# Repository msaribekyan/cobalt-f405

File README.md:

# Cobalt F405

## An open source flight controller based on the STM32F405 microcontroller

Custom designed flight controller for quadcopters and more.

<div style="text-align:center;">

</div>

## Features

Cobalt F405 flight controller has the following features:
- 4 motor outputs
- barometer and blackbox
- analog on-screen display
- easy-to-use connectors for camera and VTx
- USB Type-C connector for configuration
- high power 5 volt regulator

## Firmware

The flight controller was tested with the [Betaflight](https://github.com/betaflight/betaflight) firmware.

<div style="text-align:center;">

</div>

## Designing

KiCad was used for designing the schematic and the PCB.

### Schematic

<div style="text-align:center;">

</div>

### PCB 3D model

<div style="text-align:center;">

</div>

## Further improvements

### Microcontroller

Although the STM32F405 is still a good choice for flight controllers today, other more powerful microcontrollers also exist. [Betaflight guidlines](https://betaflight.com/docs/development/manufacturer/manufacturer-design-guidelines) suggest not using more than 4 motor outputs for STM32F4 or STM32F7 type microcontrollers.

### PCB

Two layer PCB is fine, however going to a four layer PCB with ground planes inside would reduce electrical noise, which would benefit the microcontroller and the on-board sensors.

### 9 volt regulator

Some external peripherals require higher voltage than 5 volts, however cannot accept 25 volts straight from a 6S battery. A 9 volt regulator can be added to solve this issue.

### More pads and connectors

More pads on the PCB would make it more flexible and easier to use in application. Camera and VTx connectors can be moved to more suitable locations and a connector for the radio receiver could be added.

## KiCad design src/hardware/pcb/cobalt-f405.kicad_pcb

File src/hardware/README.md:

# The hardware

The PCB was design using [KiCad](https://gitlab.com/kicad/code/kicad), an open source schematic and PCB design software.

## Microcontroller: STM32F405RGT6

Betaflight has a list of supported microcontrollers and the STM32F405RGT6, because it is the most common and economical choice while providing enough performance.

## Inertial measurement unit: ICM-42688-P

The [Betaflight Flight Controller Manufacturer Design Guidelines](https://betaflight.com/docs/development/manufacturer/manufacturer-design-guidelines) strongly recommends against using the MPU6000 as it is end-of-life. Instead ICM-42688-P is suggested.

## Barometer: BMP388

Newer model of the BMP180 and BMP280 barometers.

## Blackbox: W25Q128JVP

Winbond W25Q128JVPIQ is a cheap and common 16 MB NOR Flash chip, with a small WSON-8 footprint.

## On-screen display: AT7456E

The flight controller has an on-screen display, for use with analog video. AT7456E is the standard choice.

## Connectors

An 8 pin JST connector is the standard for connecting to the ESC. Telemetry data is connected to UART 1 RX. The two Molex PicoBlade connectors are for the camera and the video transmitter (VTx). The camera connector passes 5 volt power, while the VTx connector passes battery power for more powerful VTx and also has a SmartAudio pin connected to UART 1 TX.

## UART, I2C and power outputs

UARTs 2 and 3 are available on the solder points, along with the I2C bus and three pairs of 5 volt and ground connections.

## PCB

## Front layers

<div style="text-align:center;">

</div>

### Back layers

<div style="text-align:center;">

</div>

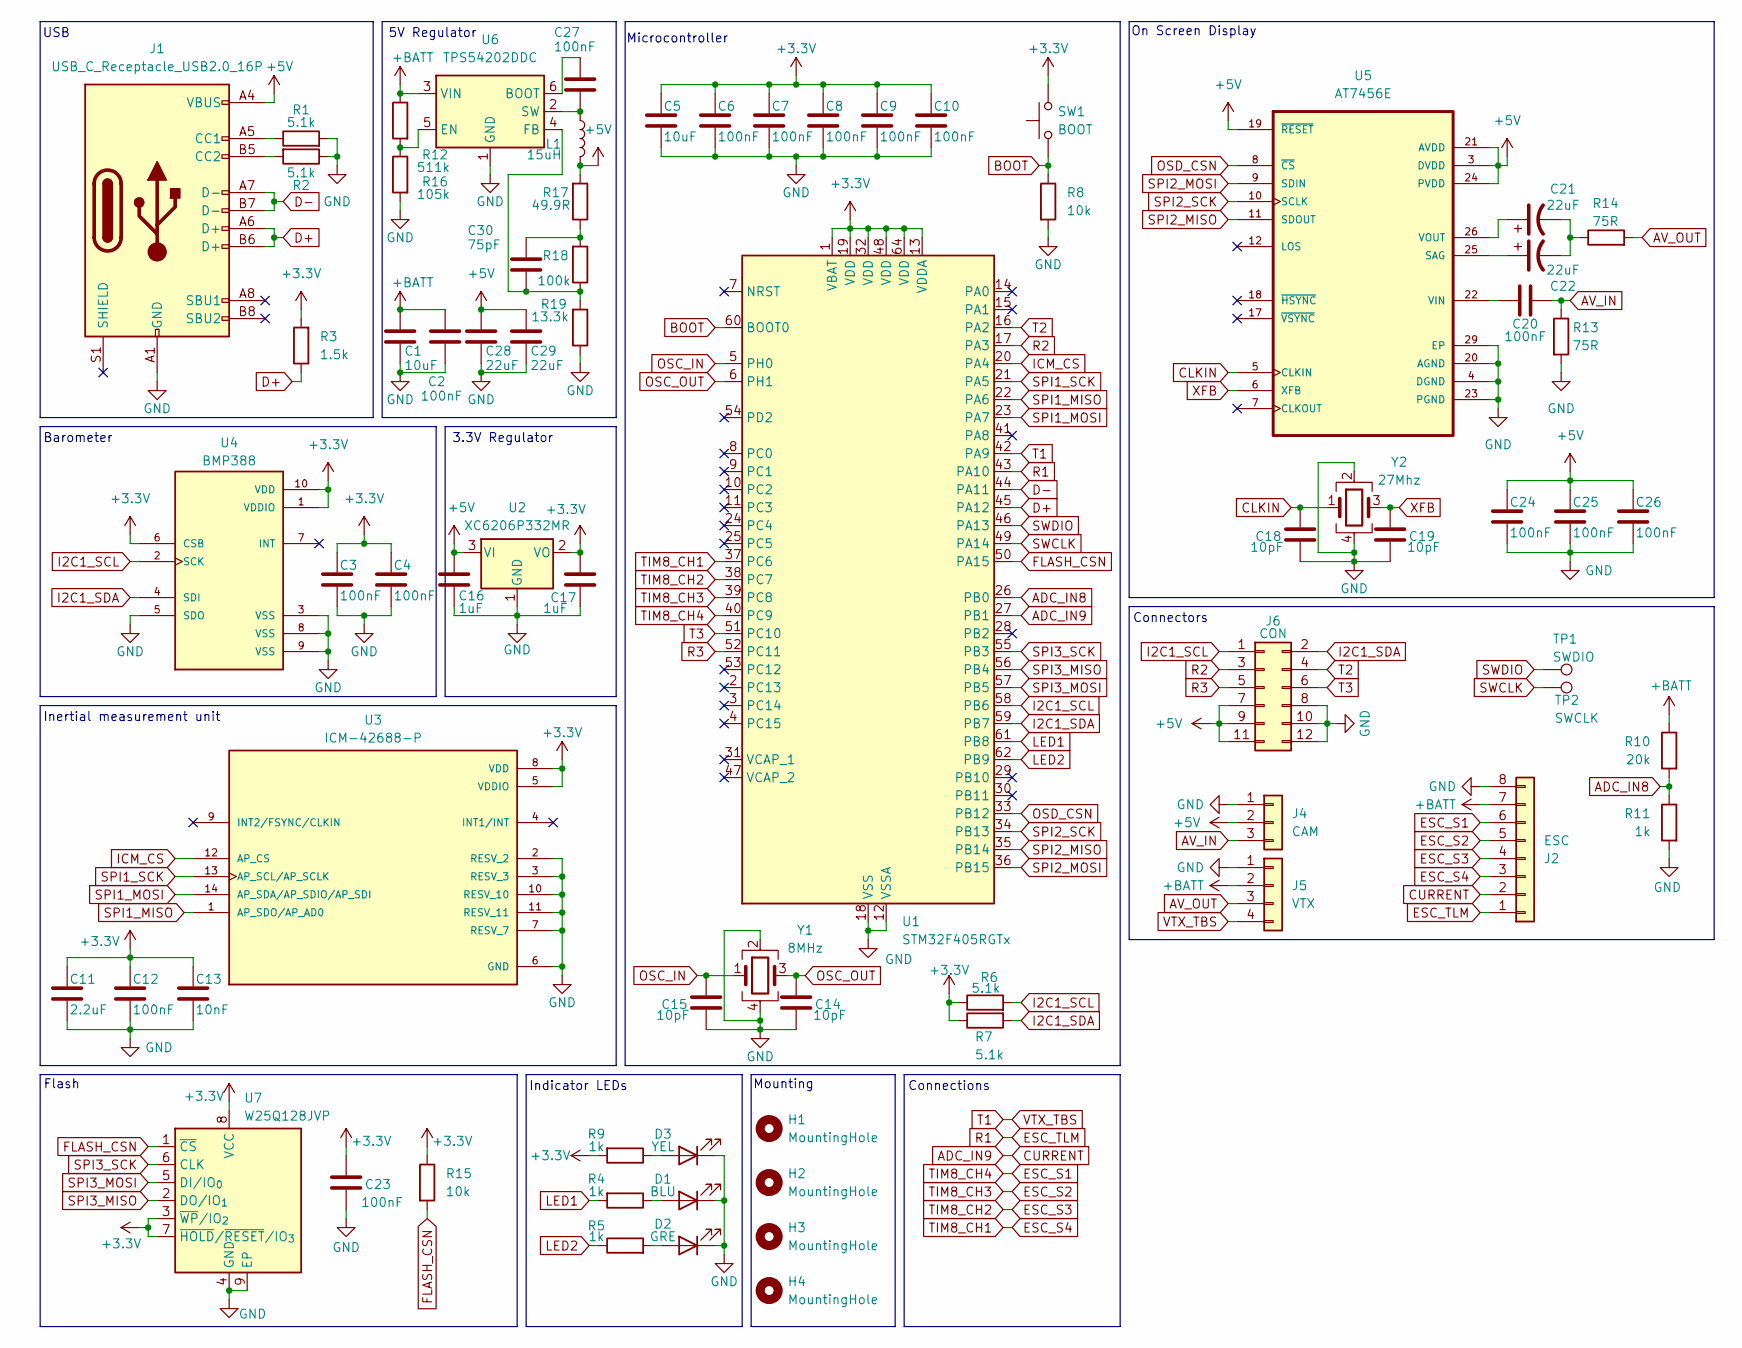
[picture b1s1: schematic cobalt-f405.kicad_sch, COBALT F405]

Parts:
C1, C5: 10uF; C_0603_1608Metric
C2, C8, C20, C23, C27: 100nF; C_0603_1608Metric
C3, C4, C6, C7, C9, C10, C12, C24, C25, C26: 100nF; C_0402_1005Metric
C11: 2.2uF; C_0402_1005Metric
C13: 10nF; C_0402_1005Metric
C14, C15, C18, C19: 10pF; C_0402_1005Metric
C16, C17: 1uF; C_0402_1005Metric
C21, C22, C28, C29: 22uF; C_0603_1608Metric
C30: 75pF; C_0603_1608Metric
D1: BLU; LED_0603_1608Metric
D2: GRE; LED_0603_1608Metric
D3: YEL; LED_0603_1608Metric
H1, H2, H3, H4: MountingHole; MountingHole_4.3mm_M4_ISO14580
J1: USB_C_Receptacle_USB2.0_16P; USB_C_Receptacle_HCTL_HC-TYPE-C-16P-01A
J2: ESC; JST_SH_SM08B-SRSS-TB_1x08-1MP_P1.00mm_Horizontal
J4: CAM; Molex_PicoBlade_53261-0371_1x03-1MP_P1.25mm_Horizontal
J5: VTX; Molex_PicoBlade_53261-0471_1x04-1MP_P1.25mm_Horizontal
J6: CON; PinSocket_2x06_P2.00mm_Vertical
L1: 15uH; L_Bourns_SRP7028A_7.3x6.6mm
R1, R2, R6, R7: 5.1k; R_0402_1005Metric
R3: 1.5k; R_0402_1005Metric
R4, R5, R9, R11: 1k; R_0603_1608Metric
R8, R15: 10k; R_0603_1608Metric
R10: 20k; R_0603_1608Metric
R12: 511k; R_0603_1608Metric
R13, R14: 75R; R_0603_1608Metric
R16: 105k; R_0402_1005Metric
R17: 49.9R; R_0402_1005Metric
R18: 100k; R_0402_1005Metric
R19: 13.3k; R_0402_1005Metric
SW1: BOOT; SW_Push_SPST_NO_Alps_SKRK
TP1: SWDIO; TestPoint_Pad_D1.0mm
TP2: SWCLK; TestPoint_Pad_D1.0mm
U1: STM32F405RGTx; LQFP-64_10x10mm_P0.5mm
U2: XC6206P332MR; SOT-23-3
U3: ICM-42688-P; PQFN50P300X250X97-14N; PARTREV 1.2
U4: BMP388; PQFN50P200X200X80-10N; PARTREV 1.1
U5: AT7456E; SOP65P637X110-28N
U6: TPS54202DDC; SOT-23-6
U7: W25Q128JVP; WSON-8-1EP_6x5mm_P1.27mm_EP3.4x4.3mm
Y1: 8MHz; Crystal_SMD_3225-4Pin_3.2x2.5mm
Y2: 27Mhz; Crystal_SMD_3225-4Pin_3.2x2.5mm

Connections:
+3.3V: C3.1, C4.1, C5.1, C6.1, C7.1, C8.1, C9.1, C10.1, C11.1, C12.1, C13.1, C17.1, C23.1, R3.2, R6.1, R7.1, R9.2, R15.1, SW1.2, U1.1 (VBAT), U1.13 (VDDA), U1.19 (VDD), U1.32 (VDD), U1.48 (VDD), U1.64 (VDD), U2.2 (VO), U3.5 (VDDIO), U3.8 (VDD), U4.1 (VDDIO), U4.6 (CSB), U4.10 (VDD), U7.3 (~WP/IO_{2}), U7.7 (~HOLD/~RESET/IO_{3}), U7.8 (VCC)
+5V: C16.1, C24.1, C25.1, C26.1, C28.1, C29.1, J1.A4 (VBUS), J1.A9 (VBUS), J1.B4 (VBUS), J1.B9 (VBUS), J4.2, J6.7, J6.9, J6.11, L1.1, R17.2, U2.3 (VI), U5.3 (DVDD), U5.19 (~RESET), U5.21 (AVDD), U5.24 (PVDD)
+BATT: C1.1, C2.1, J2.7, J5.2, R10.1, R12.1, U6.3 (VIN)
ADC_IN8: R10.2, R11.1, U1.26 (PB0)
ADC_IN9: J2.2, U1.27 (PB1)
AV_IN: C20.2, J4.3, R13.1
AV_OUT: J5.3, R14.2
BOOT: R8.1, SW1.1, U1.60 (BOOT0)
CLKIN: C18.1, U5.5 (CLKIN), Y2.1
D+: J1.A6 (D+), J1.B6 (D+), R3.1, U1.45 (PA12)
D-: J1.A7 (D-), J1.B7 (D-), U1.44 (PA11)
ESC_S1: J2.6, U1.40 (PC9)
ESC_S2: J2.5, U1.39 (PC8)
ESC_S3: J2.4, U1.38 (PC7)
ESC_S4: J2.3, U1.37 (PC6)
ESC_TLM: J2.1, U1.43 (PA10)
FLASH_CSN: R15.2, U1.50 (PA15), U7.1 (~CS)
GND: C1.2, C2.2, C3.2, C4.2, C5.2, C6.2, C7.2, C8.2, C9.2, C10.2, C11.2, C12.2, C13.2, C14.2, C15.2, C16.2, C17.2, C18.2, C19.2, C23.2, C24.2, C25.2, C26.2, C28.2, C29.2, D1.1 (K), D2.1 (K), D3.1 (K), J1.A1 (GND), J1.A12 (GND), J1.B1 (GND), J1.B12 (GND), J2.8, J4.1, J5.1, J6.8, J6.10, J6.12, R1.2, R2.1, R8.2, R11.2, R13.2, R16.2, R19.1, U1.12 (VSSA), U1.18 (VSS), U1.63 (VSS), U2.1 (GND), U3.2 (RESV_2), U3.3 (RESV_3), U3.6 (GND), U3.7 (RESV_7), U3.10 (RESV_10), U3.11 (RESV_11), U4.3 (VSS), U4.5 (SDO), U4.8 (VSS), U4.9 (VSS), U5.4 (DGND), U5.20 (AGND), U5.23 (PGND), U5.29 (EP), U6.1 (GND), U7.4 (GND), U7.9 (EP), Y1.2, Y1.4, Y2.2, Y2.4
I2C1_SCL: J6.1, R6.2, U1.58 (PB6), U4.2 (SCK)
I2C1_SDA: J6.2, R7.2, U1.59 (PB7), U4.4 (SDI)
ICM_CS: U1.20 (PA4), U3.12 (AP_CS)
LED1: R4.2, U1.61 (PB8)
LED2: R5.1, U1.62 (PB9)
unnamed: C21.2, C22.2, R14.1
unnamed: C30.2, R17.1, R18.2
unnamed: D1.2 (A), R4.1
unnamed: D2.2 (A), R5.2
unnamed: D3.2 (A), R9.1
unnamed: J1.A5 (CC1), R1.1
unnamed: J1.B5 (CC2), R2.2
unnamed: C22.1, U5.25 (SAG)
unnamed: C20.1, U5.22 (VIN)
unnamed: C21.1, U5.26 (VOUT)
unnamed: C27.2, U6.6 (BOOT)
unnamed: R12.2, R16.1, U6.5 (EN)
unnamed: C30.1, R18.1, R19.2, U6.4 (FB)
unnamed: C27.1, L1.2, U6.2 (SW)
OSC_IN: C15.1, U1.5 (PH0), Y1.1
OSC_OUT: C14.1, U1.6 (PH1), Y1.3
OSD_CSN: U1.33 (PB12), U5.8 (~CS)
R2: J6.3, U1.17 (PA3)
R3: J6.5, U1.52 (PC11)
SPI1_MISO: U1.22 (PA6), U3.1 (AP_SDO/AP_AD0)
SPI1_MOSI: U1.23 (PA7), U3.14 (AP_SDA/AP_SDIO/AP_SDI)
SPI1_SCK: U1.21 (PA5), U3.13 (AP_SCL/AP_SCLK)
SPI2_MISO: U1.35 (PB14), U5.11 (SDOUT)
SPI2_MOSI: U1.36 (PB15), U5.9 (SDIN)
SPI2_SCK: U1.34 (PB13), U5.10 (SCLK)
SPI3_MISO: U1.56 (PB4), U7.2 (DO/IO_{1})
SPI3_MOSI: U1.57 (PB5), U7.5 (DI/IO_{0})
SPI3_SCK: U1.55 (PB3), U7.6 (CLK)
SWCLK: TP2.1, U1.49 (PA14); also elsewhere on the board
SWDIO: TP1.1, U1.46 (PA13); also elsewhere on the board
T1: J5.4, U1.42 (PA9)
T2: J6.4, U1.16 (PA2)
T3: J6.6, U1.51 (PC10)
XFB: C19.1, U5.6 (XFB), Y2.3

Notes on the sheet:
Connectors
Microcontroller
5V Regulator
3.3V Regulator
Connections
Inertial measurement unit
Indicator LEDs
USB
On Screen Display
Barometer
Flash
Mounting

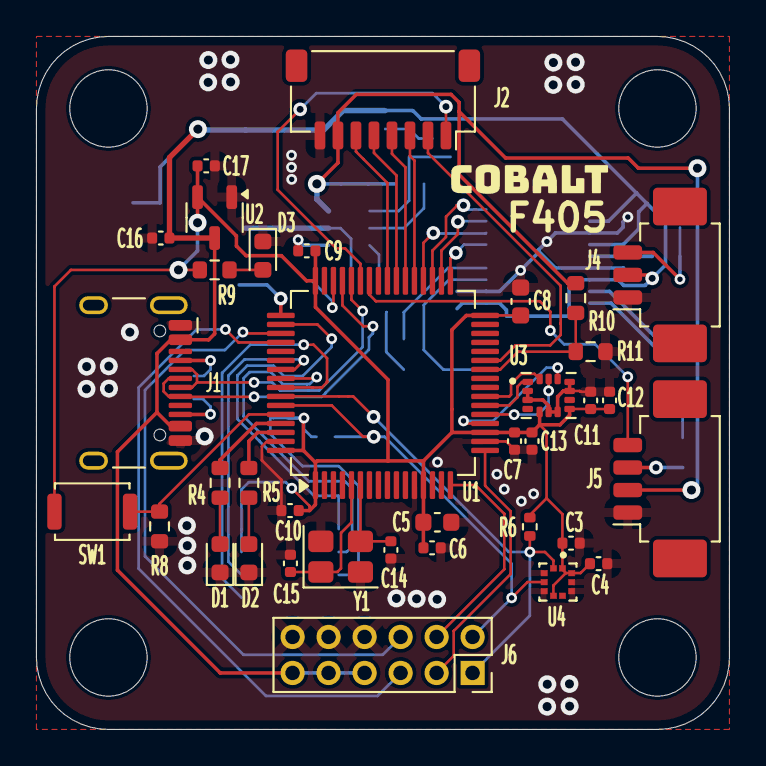
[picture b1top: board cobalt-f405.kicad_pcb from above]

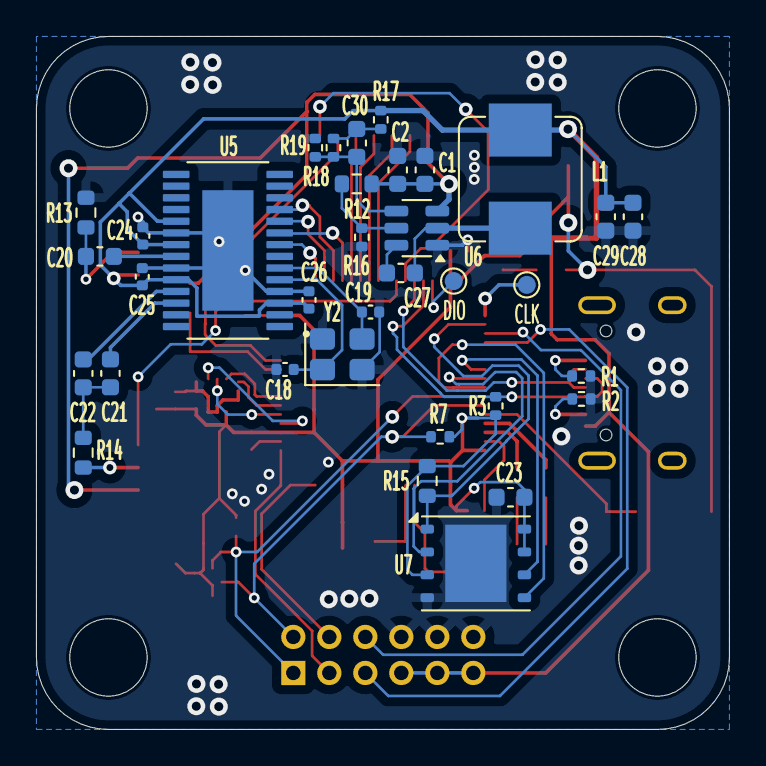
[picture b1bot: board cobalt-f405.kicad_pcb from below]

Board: 2 copper layers, 38.5 x 38.5 mm, 74 parts (34 on the bottom side), 57 nets.

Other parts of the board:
CLK: SWCLK; TestPoint_Pad_D1.0mm
DIO: SWDIO; TestPoint_Pad_D1.0mm

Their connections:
SWCLK: CLK.1; also elsewhere on the board
SWDIO: DIO.1; also elsewhere on the board

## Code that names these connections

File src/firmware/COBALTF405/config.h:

#pragma once

#define FC_TARGET_MCU			STM32F405

#define BOARD_NAME			COBALTF405
#define MANUFACTURER_ID			CBLT

#define USE_GYRO
#define USE_GYRO_SPI_ICM42688P
#define USE_ACC
#define USE_ACC_SPI_ICM42688P
#define USE_BARO_BMP388
#define USE_MAX7456
#define USE_FLASH
#define USE_FLASH_W25Q128FV

#define MOTOR1_PIN			PC9
#define MOTOR2_PIN			PC8
#define MOTOR3_PIN			PC7
#define MOTOR4_PIN			PC6

#define UART1_TX_PIN			PA9
#define UART2_TX_PIN			PA2
#define UART3_TX_PIN			PC10
#define UART1_RX_PIN			PA10
#define UART2_RX_PIN			PA3
#define UART3_RX_PIN			PC11

#define I2C1_SCL_PIN			PB6
#define I2C1_SDA_PIN			PB7

#define LED0_PIN			PB8
#define LED1_PIN			PB9

#define SPI1_SCK_PIN			PA5
#define SPI2_SCK_PIN			PB13
#define SPI3_SCK_PIN			PB3

#define SPI1_SDI_PIN			PA6
#define SPI2_SDI_PIN			PB14
#define SPI3_SDI_PIN			PB4

#define SPI1_SDO_PIN			PA7
#define SPI2_SDO_PIN			PB15
#define SPI3_SDO_PIN			PB5

#define ADC_VBAT_PIN			PB0
//#define ADC_CURR_PIN			PB1

#define FLASH_CS_PIN			PA15
#define MAX7456_SPI_CS_PIN		PB12
#define GYRO_1_CS_PIN			PA4

#define TIMER_PIN_MAPPING \
    TIMER_PIN_MAP( 0, MOTOR1_PIN, 2,  0) \
    TIMER_PIN_MAP( 1, MOTOR2_PIN, 2,  1) \
    TIMER_PIN_MAP( 2, MOTOR3_PIN, 2,  1) \
    TIMER_PIN_MAP( 3, MOTOR4_PIN, 2,  0)

#define ADC1_DMA_OPT			0
#define USE_BARO
#define BARO_I2C_INSTANCE		I2CDEV_1
//#define DEFAULT_CURRENT_METER_SOURCE    CURRENT_METER_ADC
#define DEFAULT_VOLTAGE_METER_SOURCE    VOLTAGE_METER_ADC
#define DEFAULT_VOLTAGE_METER_SCALE     210
//#define DEFAULT_CURRENT_METER_SCALE	250
//#define DEFAULT_CURRENT_METER_OFFSET	-500
#define SYSTEM_HSE_MHZ			8
#define DEFAULT_BLACKBOX_DEVICE		BLACKBOX_DEVICE_FLASH
#define MAX7456_SPI_INSTANCE		SPI2
#define FLASH_SPI_INSTANCE		SPI3
#define GYRO_1_SPI_INSTANCE		SPI1
#define GYRO_1_ALIGN			CW90_DEG
#define SERIALRX_UART			SERIAL_PORT_USART2
#define DEFAULT_RX_FEATURE		FEATURE_RX_SERIAL

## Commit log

2025-09-07 Cobalt F405 V1.0
2025-09-09 Fixed readme
